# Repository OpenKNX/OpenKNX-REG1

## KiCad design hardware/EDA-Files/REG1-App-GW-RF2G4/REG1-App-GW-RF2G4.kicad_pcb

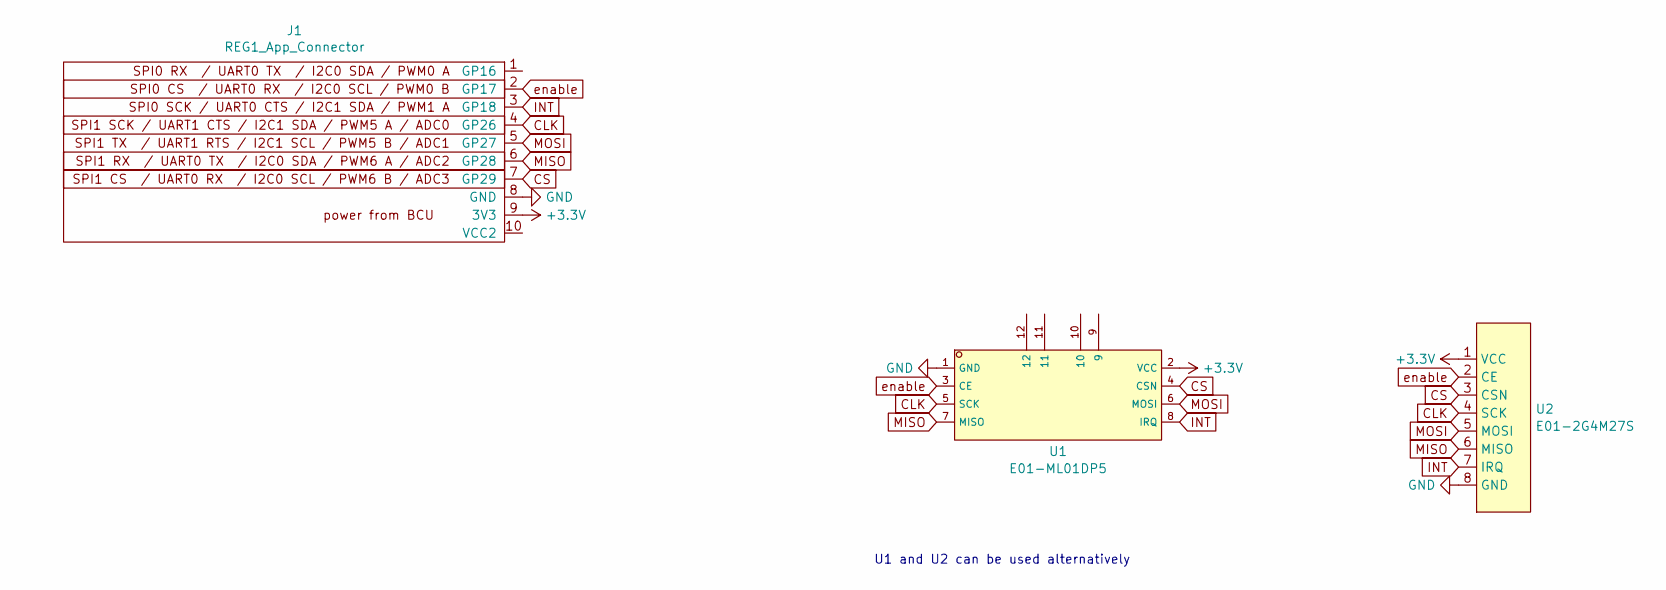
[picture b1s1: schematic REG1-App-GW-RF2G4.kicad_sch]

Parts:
J1: REG1_App_Connector; PinHeader_1x10_P2.54mm_Horizontal
U1: E01-ML01DP5; WIRELM-TH_E01-ML01DP5; LCSC C97339
U2: E01-2G4M27S; C2971732_WIRELM-SMD_10P-L23.0-W14.0-P1.27_E01-2G4M27S_Hands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; LCSC Part C2971732

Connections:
+3.3V: J1.9 (3V3), U1.2 (VCC), U2.1 (VCC)
CLK: J1.4 (GP26), U1.5 (SCK), U2.4 (SCK)
CS: J1.7 (GP29), U1.4 (CSN), U2.3 (CSN)
GND: J1.8 (GND), U1.1 (GND), U2.8 (GND), U2.9 (GND), U2.10 (GND)
INT: J1.3 (GP18), U1.8 (IRQ), U2.7 (IRQ)
MISO: J1.6 (GP28), U1.7 (MISO), U2.6 (MISO)
MOSI: J1.5 (GP27), U1.6 (MOSI), U2.5 (MOSI)
enable: J1.2 (GP17), U1.3 (CE), U2.2 (CE)

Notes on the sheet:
U1 and U2 can be used alternatively

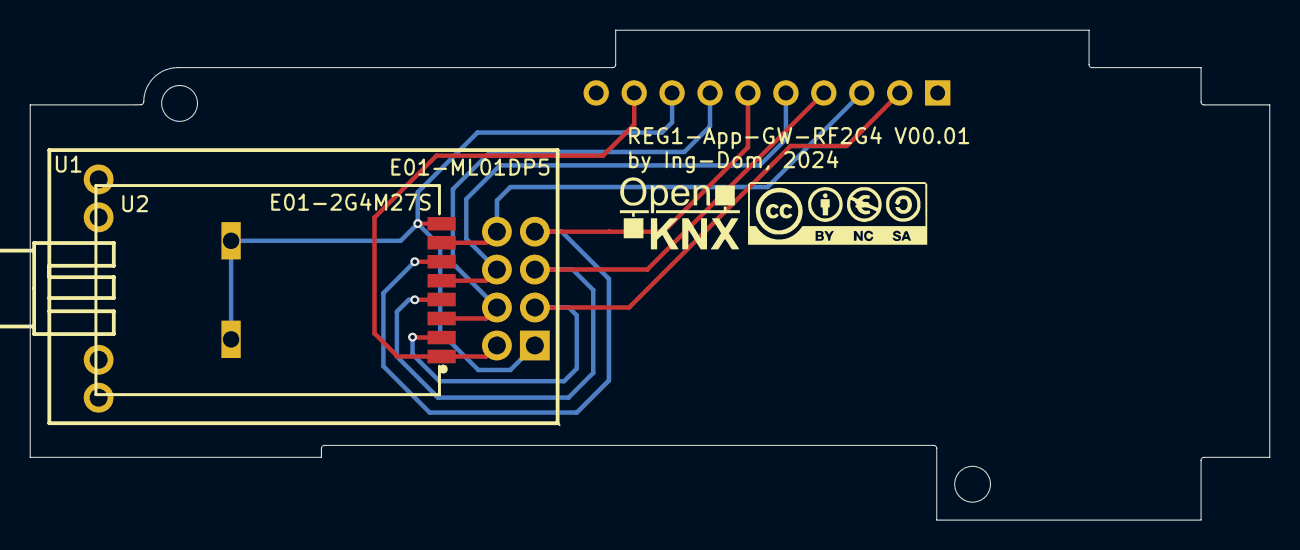
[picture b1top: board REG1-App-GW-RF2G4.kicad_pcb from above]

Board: 2 copper layers, 83.0 x 32.8 mm, 4 parts (1 on the bottom side), 8 nets.

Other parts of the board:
G1: LOGO; CC-BY-NY-SA_12x4

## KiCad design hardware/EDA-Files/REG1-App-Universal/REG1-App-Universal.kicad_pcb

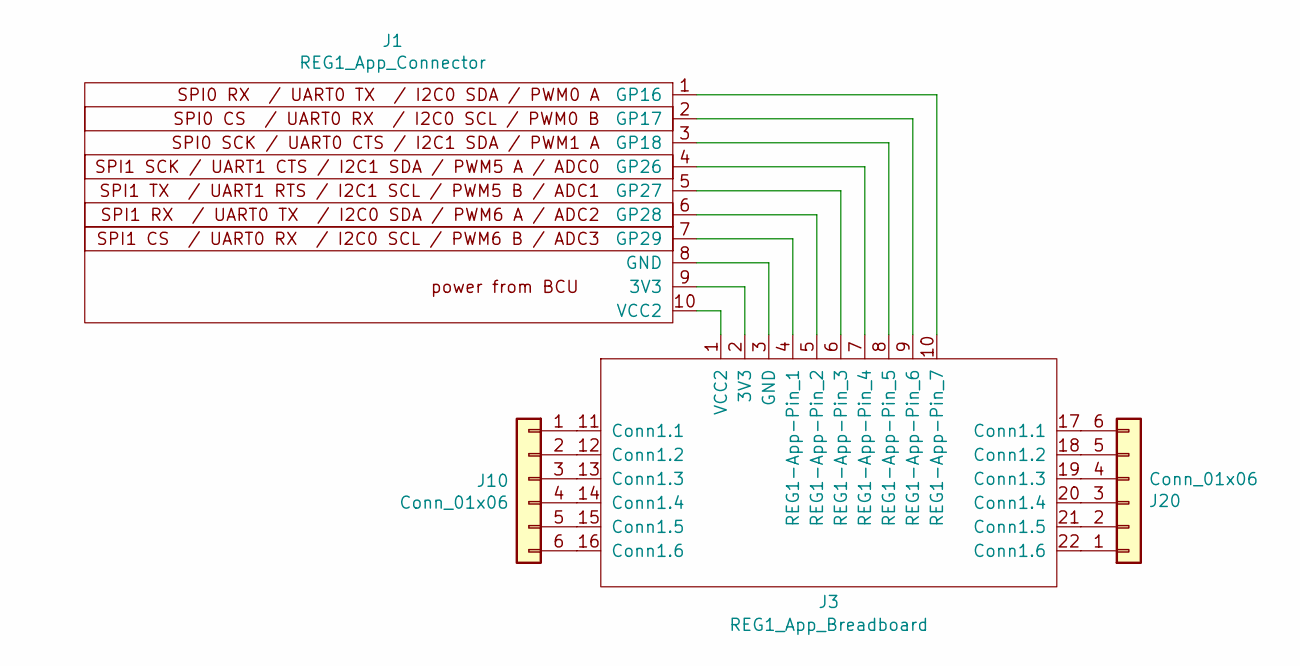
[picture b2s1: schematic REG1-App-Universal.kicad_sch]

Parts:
J1: REG1_App_Connector; PinHeader_1x10_P2.54mm_Horizontal; LCSC C706873
J3: REG1_App_Breadboard
J10, J20: Conn_01x06; PhoenixContact_MC_1,5_6-G-3.5_1x06_P3.50mm_Horizontal; LCSC C441175

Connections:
unnamed: J1.9 (3V3), J3.2 (3V3)
unnamed: J1.8 (GND), J3.3 (GND)
unnamed: J1.1 (GP16), J3.10 (REG1-App-Pin_7)
unnamed: J1.2 (GP17), J3.9 (REG1-App-Pin_6)
unnamed: J1.3 (GP18), J3.8 (REG1-App-Pin_5)
unnamed: J1.4 (GP26), J3.7 (REG1-App-Pin_4)
unnamed: J1.5 (GP27), J3.6 (REG1-App-Pin_3)
unnamed: J1.6 (GP28), J3.5 (REG1-App-Pin_2)
unnamed: J1.7 (GP29), J3.4 (REG1-App-Pin_1)
unnamed: J1.10 (VCC2), J3.1 (VCC2)
unnamed: J3.11 (Conn1.1), J10.1
unnamed: J3.12 (Conn1.2), J10.2
unnamed: J3.13 (Conn1.3), J10.3
unnamed: J3.14 (Conn1.4), J10.4
unnamed: J3.15 (Conn1.5), J10.5
unnamed: J3.16 (Conn1.6), J10.6
unnamed: J3.22 (Conn1.6), J20.1
unnamed: J3.21 (Conn1.5), J20.2
unnamed: J3.20 (Conn1.4), J20.3
unnamed: J3.19 (Conn1.3), J20.4
unnamed: J3.18 (Conn1.2), J20.5
unnamed: J3.17 (Conn1.1), J20.6

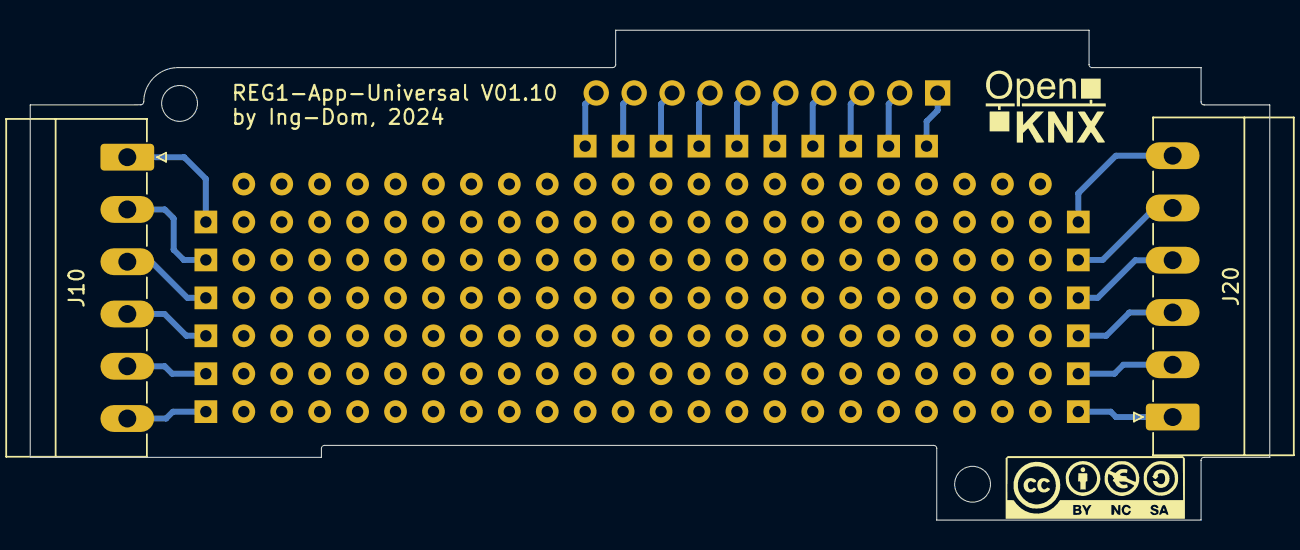
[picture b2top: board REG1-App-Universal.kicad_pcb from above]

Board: 2 copper layers, 83.0 x 32.8 mm, 6 parts (1 on the bottom side), 22 nets.

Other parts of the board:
G*: LOGO; CC-BY-NY-SA_12x4
G*#2: LOGO; OpenKNX_Logo_10x10

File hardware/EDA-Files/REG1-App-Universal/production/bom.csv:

Designator,Footprint,Quantity,Value,LCSC Part #
J1,PinHeader_1x10_P2.54mm_Horizontal,1,REG1_App_Connector,C706873
"J10, J20","PhoenixContact_MC_1,5_6-G-3.5_1x06_P3.50mm_Horizontal",2,Conn_01x06,C441175
J3,REG1_App_Breadboard,1,REG1_App_Breadboard,

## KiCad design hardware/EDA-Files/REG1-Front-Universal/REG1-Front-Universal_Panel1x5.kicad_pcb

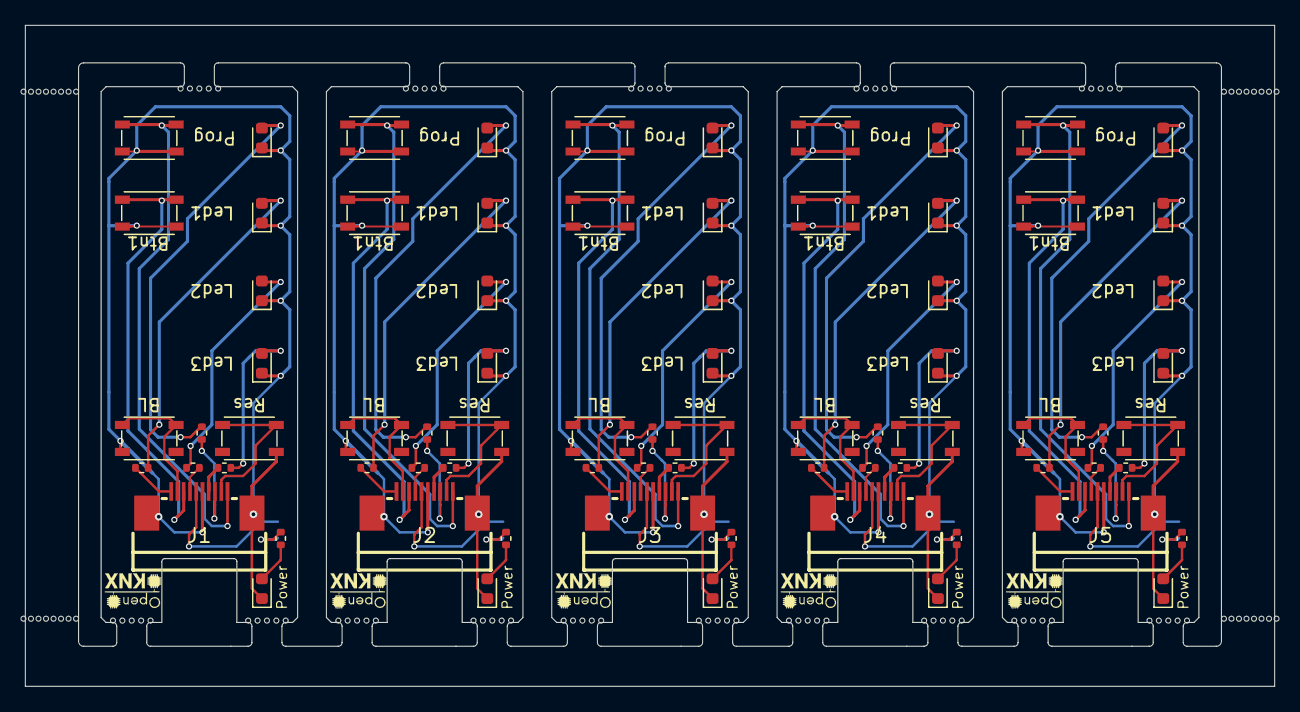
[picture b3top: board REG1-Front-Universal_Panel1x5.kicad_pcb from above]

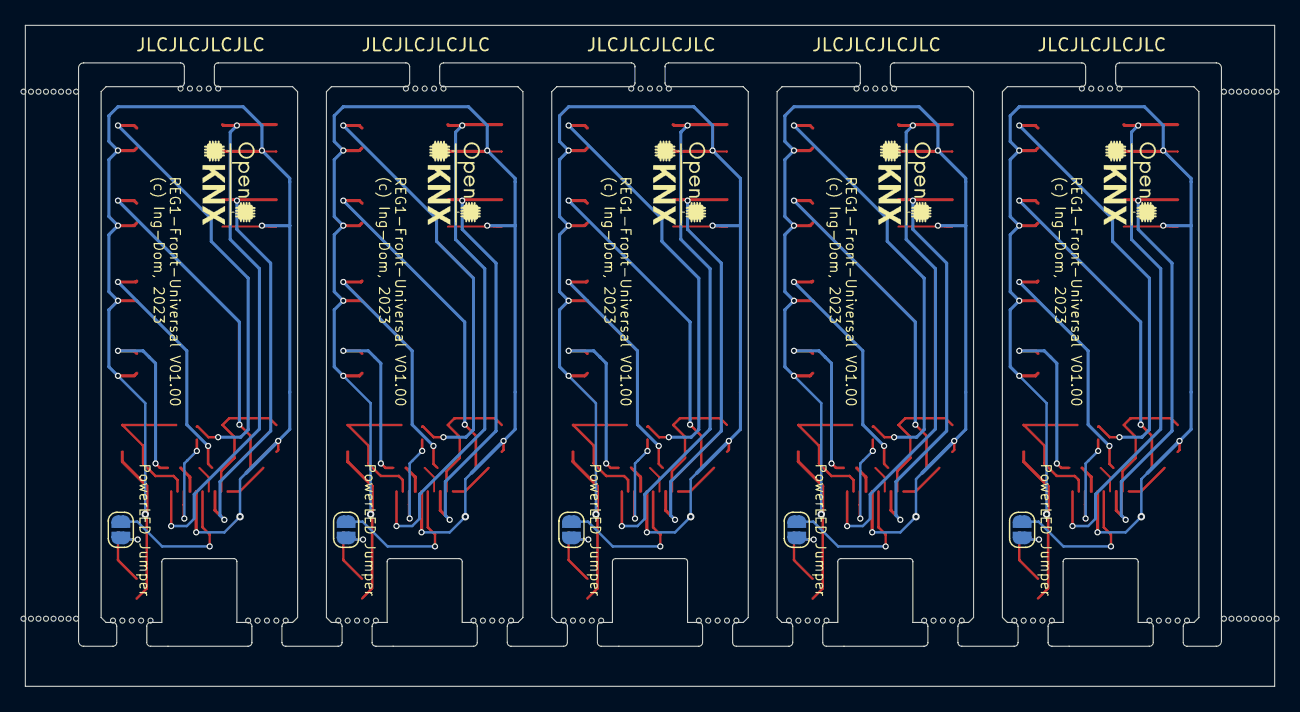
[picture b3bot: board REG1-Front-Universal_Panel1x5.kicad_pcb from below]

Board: 2 copper layers, 99.8 x 52.8 mm, 99 parts (5 on the bottom side), 16 nets.

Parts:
D1, D6, D11, D16, D21: Prog; LED_0603_1608Metric
D2, D7, D12, D17, D22: Led1; LED_0603_1608Metric
D3, D8, D13, D18, D23: Led2; LED_0603_1608Metric
D4, D9, D14, D19, D24: Led3; LED_0603_1608Metric
D5, D10, D15, D20, D25: Power; LED_0603_1608Metric
J1, J2, J3, J4, J5: Frontpanel; C11050_FPC-SMD_P0.5-10P_LSXJ-H2.0-10P
JP1, JP2, JP3, JP4, JP5: PowerLED Jumper; SolderJumper-2_P1.3mm_Open_RoundedPad1.0x1.5mm
R1, R2, R3, R4, R5, R6, R7, R8, R9, R10, R11, R12, R13, R14, R15, R16, R17, R18, R19, R20, R21, R22, R23, R24, R25: 2k2; R_0402_1005Metric
SW1, SW5, SW9, SW13, SW17: Prog; C455282_SW-SMD_4P-L4.2-W3.3-P2.15-LS5.1
SW2, SW6, SW10, SW14, SW18: Btn1; C455282_SW-SMD_4P-L4.2-W3.3-P2.15-LS5.1
SW3, SW7, SW11, SW15, SW19: Res; C455282_SW-SMD_4P-L4.2-W3.3-P2.15-LS5.1
SW4, SW8, SW12, SW16, SW20: BL; C455282_SW-SMD_4P-L4.2-W3.3-P2.15-LS5.1
e: VAL**; mouse-bite-5.00mm-frame
e#2: VAL**; mouse-bite-5.00mm-frame
mouse-bite, mouse-bite1, mouse-bite2, mouse-bite3, mouse-bite4, mouse-bite5, mouse-bite6, mouse-bite7, mouse-bite8, mouse-bite9, mouse-bite10, mouse-bite11, mouse-bite12: mouse-bite-2.00mm-slot_1side
mouse-bite#2, mouse-bite#4: VAL**; mouse-bite-5.00mm-frame
mouse-bite#3, mouse-bite#5: mouse-bite-2.00mm-slot_1side

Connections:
+3.3V: J1.6, J2.6, J3.6, J4.6, J5.6, JP1.2 (B), JP2.2 (B), JP3.2 (B), JP4.2 (B), JP5.2 (B)
BOOTSEL: J1.9, J2.9, J3.9, J4.9, J5.9, SW4.1, SW8.1, SW12.1, SW16.1, SW20.1
GND: D1.1 (K), D2.1 (K), D3.1 (K), D4.1 (K), D5.1 (K), D6.1 (K), D7.1 (K), D8.1 (K), D9.1 (K), D10.1 (K), D11.1 (K), D12.1 (K), D13.1 (K), D14.1 (K), D15.1 (K), D16.1 (K), D17.1 (K), D18.1 (K), D19.1 (K), D20.1 (K), D21.1 (K), D22.1 (K), D23.1 (K), D24.1 (K), D25.1 (K), J1.5, J1.11, J1.12, J2.5, J2.11, J2.12, J3.5, J3.11, J3.12, J4.5, J4.11, J4.12, J5.5, J5.11, J5.12, SW1.2, SW2.2, SW3.2, SW4.2, SW5.2, SW6.2, SW7.2, SW8.2, SW9.2, SW10.2, SW11.2, SW12.2, SW13.2, SW14.2, SW15.2, SW16.2, SW17.2, SW18.2, SW19.2, SW20.2
GPIO6: J1.10, J2.10, J3.10, J4.10, J5.10, R2.2, R7.2, R12.2, R17.2, R22.2
GPIO7: J1.8, J2.8, J3.8, J4.8, J5.8, SW2.1, SW6.1, SW10.1, SW14.1, SW18.1
GPIO22: J1.4, J2.4, J3.4, J4.4, J5.4, R4.2, R9.2, R14.2, R19.2, R24.2
GPIO23: J1.1, J2.1, J3.1, J4.1, J5.1, SW1.1, SW5.1, SW9.1, SW13.1, SW17.1
GPIO24: J1.7, J2.7, J3.7, J4.7, J5.7, R3.2, R8.2, R13.2, R18.2, R23.2
GPIO25: J1.3, J2.3, J3.3, J4.3, J5.3, R1.2, R6.2, R11.2, R16.2, R21.2
unnamed: D1.2 (A), D6.2 (A), D11.2 (A), D16.2 (A), D21.2 (A), R1.1, R6.1, R11.1, R16.1, R21.1
unnamed: D2.2 (A), D7.2 (A), D12.2 (A), D17.2 (A), D22.2 (A), R2.1, R7.1, R12.1, R17.1, R22.1
unnamed: D3.2 (A), D8.2 (A), D13.2 (A), D18.2 (A), D23.2 (A), R3.1, R8.1, R13.1, R18.1, R23.1
unnamed: D4.2 (A), D9.2 (A), D14.2 (A), D19.2 (A), D24.2 (A), R4.1, R9.1, R14.1, R19.1, R24.1
unnamed: D5.2 (A), D10.2 (A), D15.2 (A), D20.2 (A), D25.2 (A), R5.1, R10.1, R15.1, R20.1, R25.1
unnamed: JP1.1 (A), JP2.1 (A), JP3.1 (A), JP4.1 (A), JP5.1 (A), R5.2, R10.2, R15.2, R20.2, R25.2
RUN: J1.2, J2.2, J3.2, J4.2, J5.2, SW3.1, SW7.1, SW11.1, SW15.1, SW19.1

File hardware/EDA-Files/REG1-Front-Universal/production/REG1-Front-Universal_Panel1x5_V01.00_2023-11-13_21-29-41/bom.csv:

Designator,Footprint,Quantity,Value,LCSC Part #
"D1, D11, D16, D21, D6",0603,5,Prog,C2286
"D10, D15, D20, D25, D5",0603,5,Power,C72043
"D12, D17, D2, D22, D7",0603,5,Led1,C72043
"D13, D18, D23, D3, D8",0603,5,Led2,C72043
"D14, D19, D24, D4, D9",0603,5,Led3,C72043
"J1, J2, J3, J4, J5",C11050_FPC-SMD_P0.5-10P_LSXJ-H2.0-10P,5,Frontpanel,C11050
"R1, R10, R11, R12, R13, R14, R15, R16, R17, R18, R19, R2, R20, R21, R22, R23, R24, R25, R3, R4, R5, R6, R7, R8, R9",0402,25,2k2,C25879
"SW1, SW13, SW17, SW5, SW9",C455282_SW-SMD_4P-L4.2-W3.3-P2.15-LS5.1,5,Prog,C455282
"SW10, SW14, SW18, SW2, SW6",C455282_SW-SMD_4P-L4.2-W3.3-P2.15-LS5.1,5,Btn1,C455282
"SW11, SW15, SW19, SW3, SW7",C455282_SW-SMD_4P-L4.2-W3.3-P2.15-LS5.1,5,Res,C455282
"SW12, SW16, SW20, SW4, SW8",C455282_SW-SMD_4P-L4.2-W3.3-P2.15-LS5.1,5,BL,C455282

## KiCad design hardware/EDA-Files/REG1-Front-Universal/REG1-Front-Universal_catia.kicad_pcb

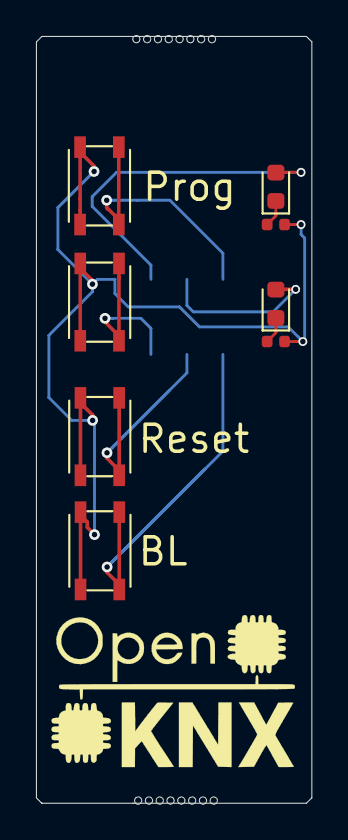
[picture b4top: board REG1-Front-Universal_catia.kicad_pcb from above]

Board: 2 copper layers, 15.3 x 42.6 mm, 11 parts (1 on the bottom side), 9 nets.

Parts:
D1: Prog; LED_0603_1608Metric
D2: Func; LED_0603_1608Metric
J1: Conn_02x04_Odd_Even; PinHeader_2x04_P2.00mm_Vertical_SMD
R1, R2: R; R_0402_1005Metric
SW1: Prog; SW_Push_Xunpu_TS-1089S
SW2: Func; SW_Push_Xunpu_TS-1089S
SW3: Res; SW_Push_Xunpu_TS-1089S
SW4: BL; SW_Push_Xunpu_TS-1089S
mouse-bite: VAL**; mouse-bite-5.00mm-frame
mouse-bite#2: VAL**; mouse-bite-5.00mm-frame

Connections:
BOOTSEL_F: J1.8, SW4.1
GND: J1.1, R1.1, R2.1, SW1.2, SW2.2, SW3.2, SW4.2
GPIO03: D2.2, J1.5
GPIO24: J1.4, SW2.1
unnamed: D1.1, R1.2
unnamed: D2.1, R2.2
PROGBTN: J1.7, SW1.1
PROGLED: D1.2, J1.3
RUN: J1.6, SW3.1

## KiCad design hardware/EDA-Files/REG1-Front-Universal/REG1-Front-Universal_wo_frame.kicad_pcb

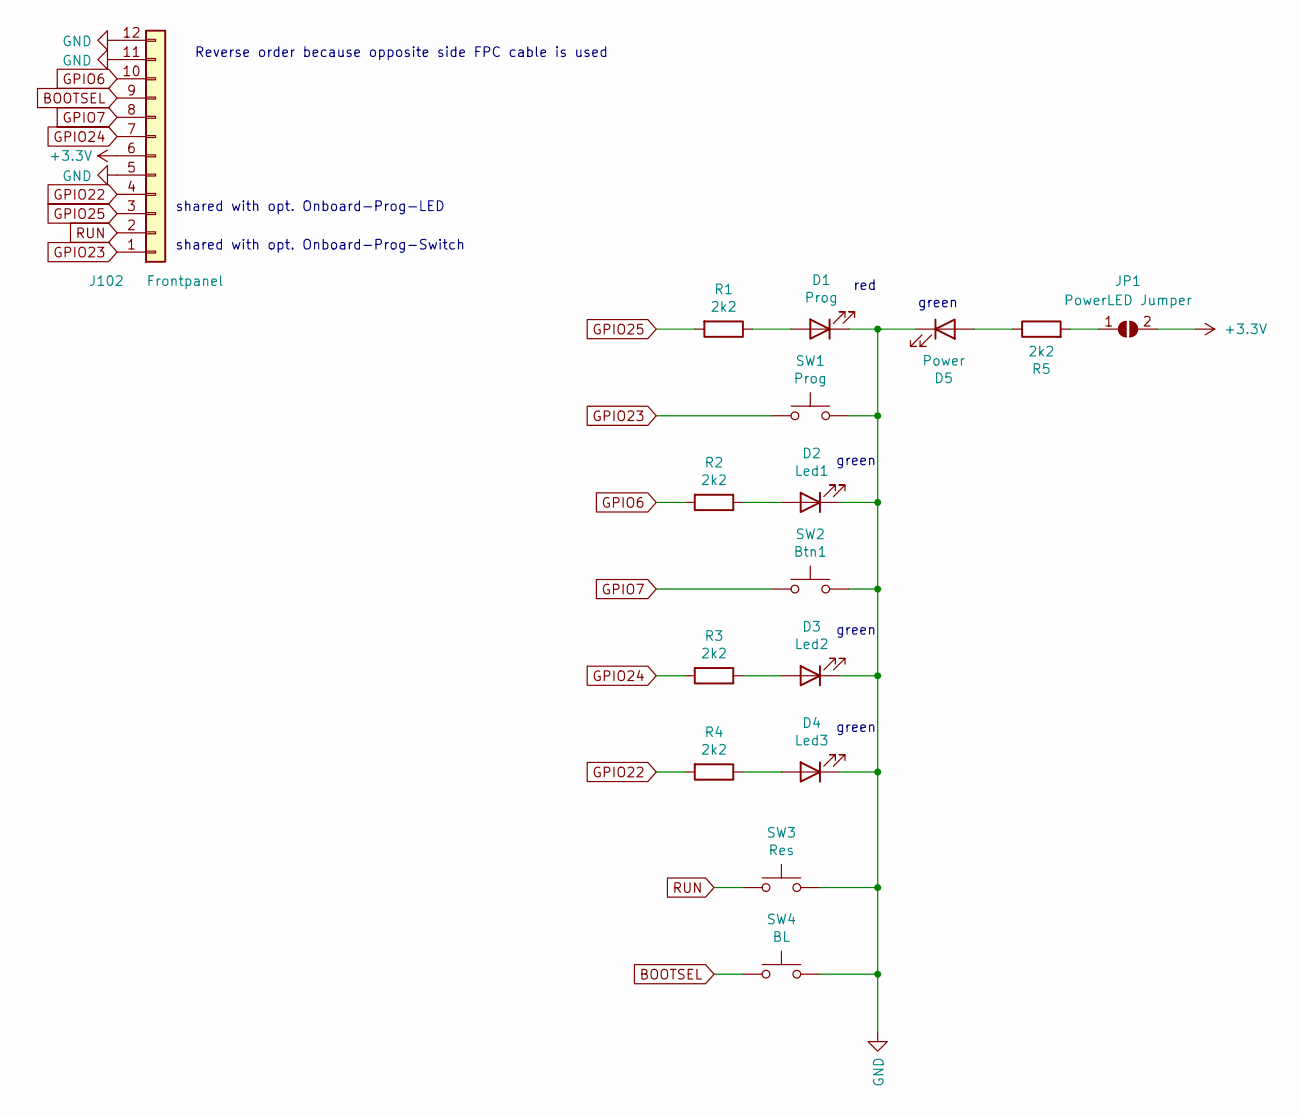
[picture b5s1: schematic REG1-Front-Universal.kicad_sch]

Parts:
D1: Prog; LED_0603_1608Metric; LCSC C2286
D2: Led1; LED_0603_1608Metric; LCSC C72043
D3: Led2; LED_0603_1608Metric; LCSC C72043
D4: Led3; LED_0603_1608Metric; LCSC C72043
D5: Power; LED_0603_1608Metric; LCSC C72043
J102: Frontpanel; C11050_FPC-SMD_P0.5-10P_LSXJ-H2.0-10P; LCSC C11050
JP1: PowerLED Jumper; SolderJumper-2_P1.3mm_Open_RoundedPad1.0x1.5mm
R1, R2, R3, R4, R5: 2k2; R_0402_1005Metric; LCSC C25879
SW1: Prog; C455282_SW-SMD_4P-L4.2-W3.3-P2.15-LS5.1; LCSC C455282
SW2: Btn1; C455282_SW-SMD_4P-L4.2-W3.3-P2.15-LS5.1; LCSC C455282
SW3: Res; C455282_SW-SMD_4P-L4.2-W3.3-P2.15-LS5.1; LCSC C455282
SW4: BL; C455282_SW-SMD_4P-L4.2-W3.3-P2.15-LS5.1; LCSC C455282

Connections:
+3.3V: JP1.2 (B); also elsewhere on the board
BOOTSEL: SW4.1; also elsewhere on the board
GND: D1.1 (K), D2.1 (K), D3.1 (K), D4.1 (K), D5.1 (K), SW1.2, SW2.2, SW3.2, SW4.2; also elsewhere on the board
GPIO6: R2.2; also elsewhere on the board
GPIO7: SW2.1; also elsewhere on the board
GPIO22: R4.2; also elsewhere on the board
GPIO23: SW1.1; also elsewhere on the board
GPIO24: R3.2; also elsewhere on the board
GPIO25: R1.2; also elsewhere on the board
unnamed: D1.2 (A), R1.1
unnamed: D2.2 (A), R2.1
unnamed: D3.2 (A), R3.1
unnamed: D4.2 (A), R4.1
unnamed: D5.2 (A), R5.1
unnamed: JP1.1 (A), R5.2
RUN: SW3.1; also elsewhere on the board

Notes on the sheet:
green
red
Reverse order because opposite side FPC cable is used
shared with opt. Onboard-Prog-Switch
shared with opt. Onboard-Prog-LED

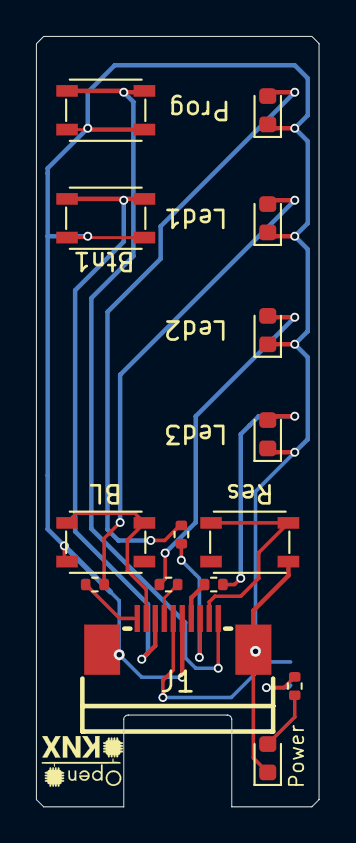
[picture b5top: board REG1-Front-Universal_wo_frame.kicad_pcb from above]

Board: 2 copper layers, 15.7 x 42.8 mm, 16 parts (1 on the bottom side), 16 nets.

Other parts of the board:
J1: Frontpanel; C11050_FPC-SMD_P0.5-10P_LSXJ-H2.0-10P

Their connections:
+3.3V: J1.6; also elsewhere on the board
BOOTSEL: J1.9; also elsewhere on the board
GND: J1.5, J1.11, J1.12; also elsewhere on the board
GPIO6: J1.10; also elsewhere on the board
GPIO7: J1.8; also elsewhere on the board
GPIO22: J1.4; also elsewhere on the board
GPIO23: J1.1; also elsewhere on the board
GPIO24: J1.7; also elsewhere on the board
GPIO25: J1.3; also elsewhere on the board
RUN: J1.2; also elsewhere on the board

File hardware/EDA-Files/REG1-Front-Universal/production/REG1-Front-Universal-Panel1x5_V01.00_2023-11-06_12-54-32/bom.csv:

Designator,Footprint,Quantity,Value,LCSC Part #
"D1_5, D1_4, D1_3, D1_2, D1",0603,5,Prog,C2286
"D2_5, D2_4, D2_3, D2_2, D2",0603,5,Led1,C72043
"D3_5, D3_4, D3_3, D3_2, D3",0603,5,Led2,C72043
"D4_5, D4_4, D4_3, D4_2, D4",0603,5,Led3,C72043
"D5_5, D5_4, D5_3, D5_2, D5",0603,5,Power,C72043
"J1_5, J1_4, J1_3, J1_2, J1",C11050_FPC-SMD_P0.5-10P_LSXJ-H2.0-10P,5,Frontpanel,C11050
"R1_5, R1_4, R1_3, R1_2, R1, R2_5, R2_4, R2_3, R2_2, R2, R3_5, R3_4, R3_3, R3_2, R3, R4_5, R4_4, R4_3, R4_2, R4, R5_5, R5_4, R5_3, R5_2, R5",0402,25,2k2,C25879
"SW1_5, SW1_4, SW1_3, SW1_2, SW1",C455282_SW-SMD_4P-L4.2-W3.3-P2.15-LS5.1,5,Prog,C455282
"SW2_5, SW2_4, SW2_3, SW2_2, SW2",C455282_SW-SMD_4P-L4.2-W3.3-P2.15-LS5.1,5,Btn1,C455282
"SW3_5, SW3_4, SW3_3, SW3_2, SW3",C455282_SW-SMD_4P-L4.2-W3.3-P2.15-LS5.1,5,Res,C455282
"SW4_5, SW4_4, SW4_3, SW4_2, SW4",C455282_SW-SMD_4P-L4.2-W3.3-P2.15-LS5.1,5,BL,C455282

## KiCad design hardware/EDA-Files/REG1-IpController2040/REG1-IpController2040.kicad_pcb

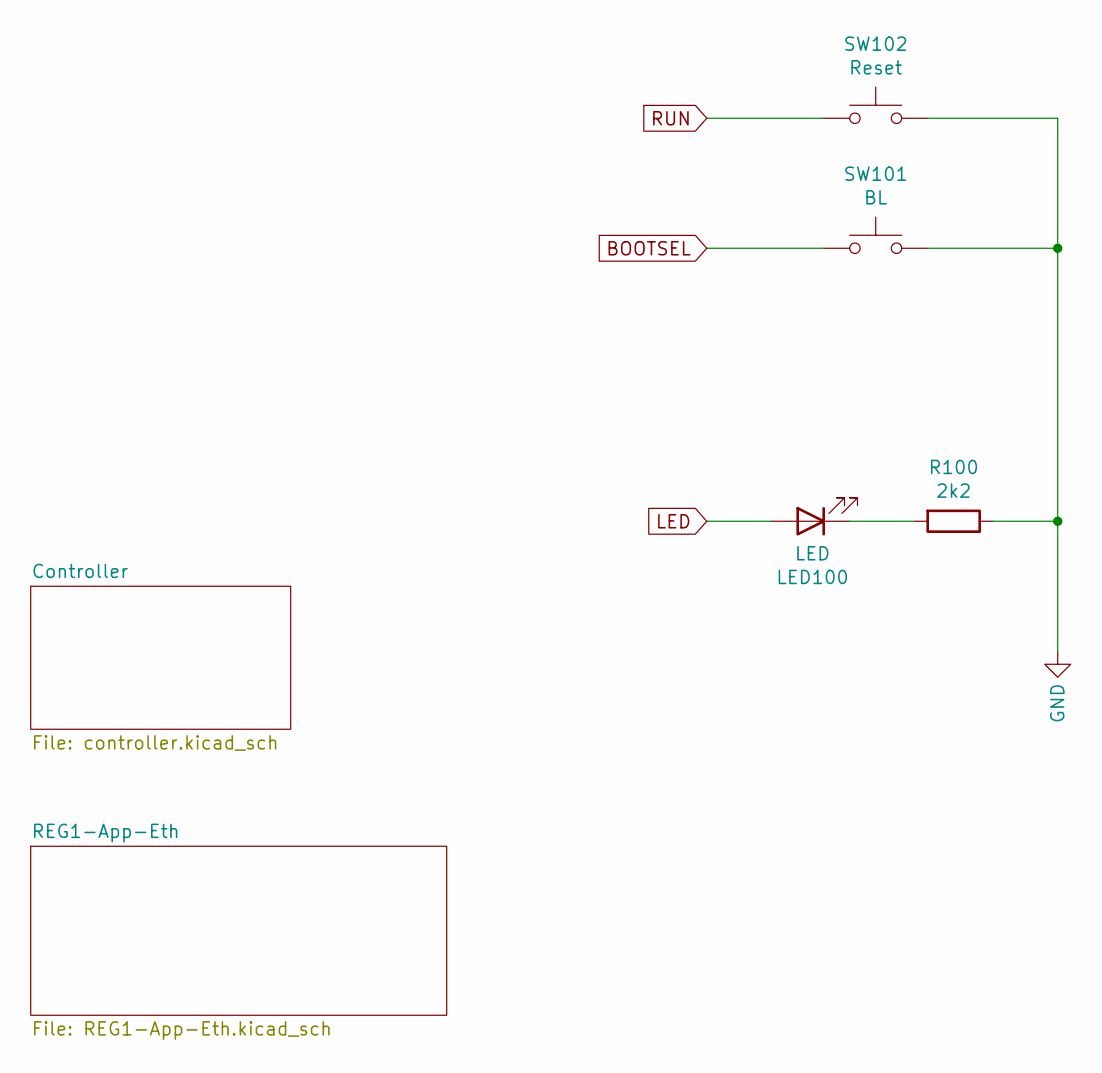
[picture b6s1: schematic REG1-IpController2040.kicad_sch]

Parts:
LED100: LED; D_0603_1608Metric
R100: 2k2; R_0402_1005Metric
SW101: BL; C455282_SW-SMD_4P-L4.2-W3.3-P2.15-LS5.1_Handsolder
SW102: Reset; C455282_SW-SMD_4P-L4.2-W3.3-P2.15-LS5.1_Handsolder

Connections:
BOOTSEL: SW101.1; also elsewhere on the board
GND: R100.1, SW101.2, SW102.2; also elsewhere on the board
LED: LED100.2 (A); also elsewhere on the board
unnamed: LED100.1 (K), R100.2
RUN: SW102.1; also elsewhere on the board

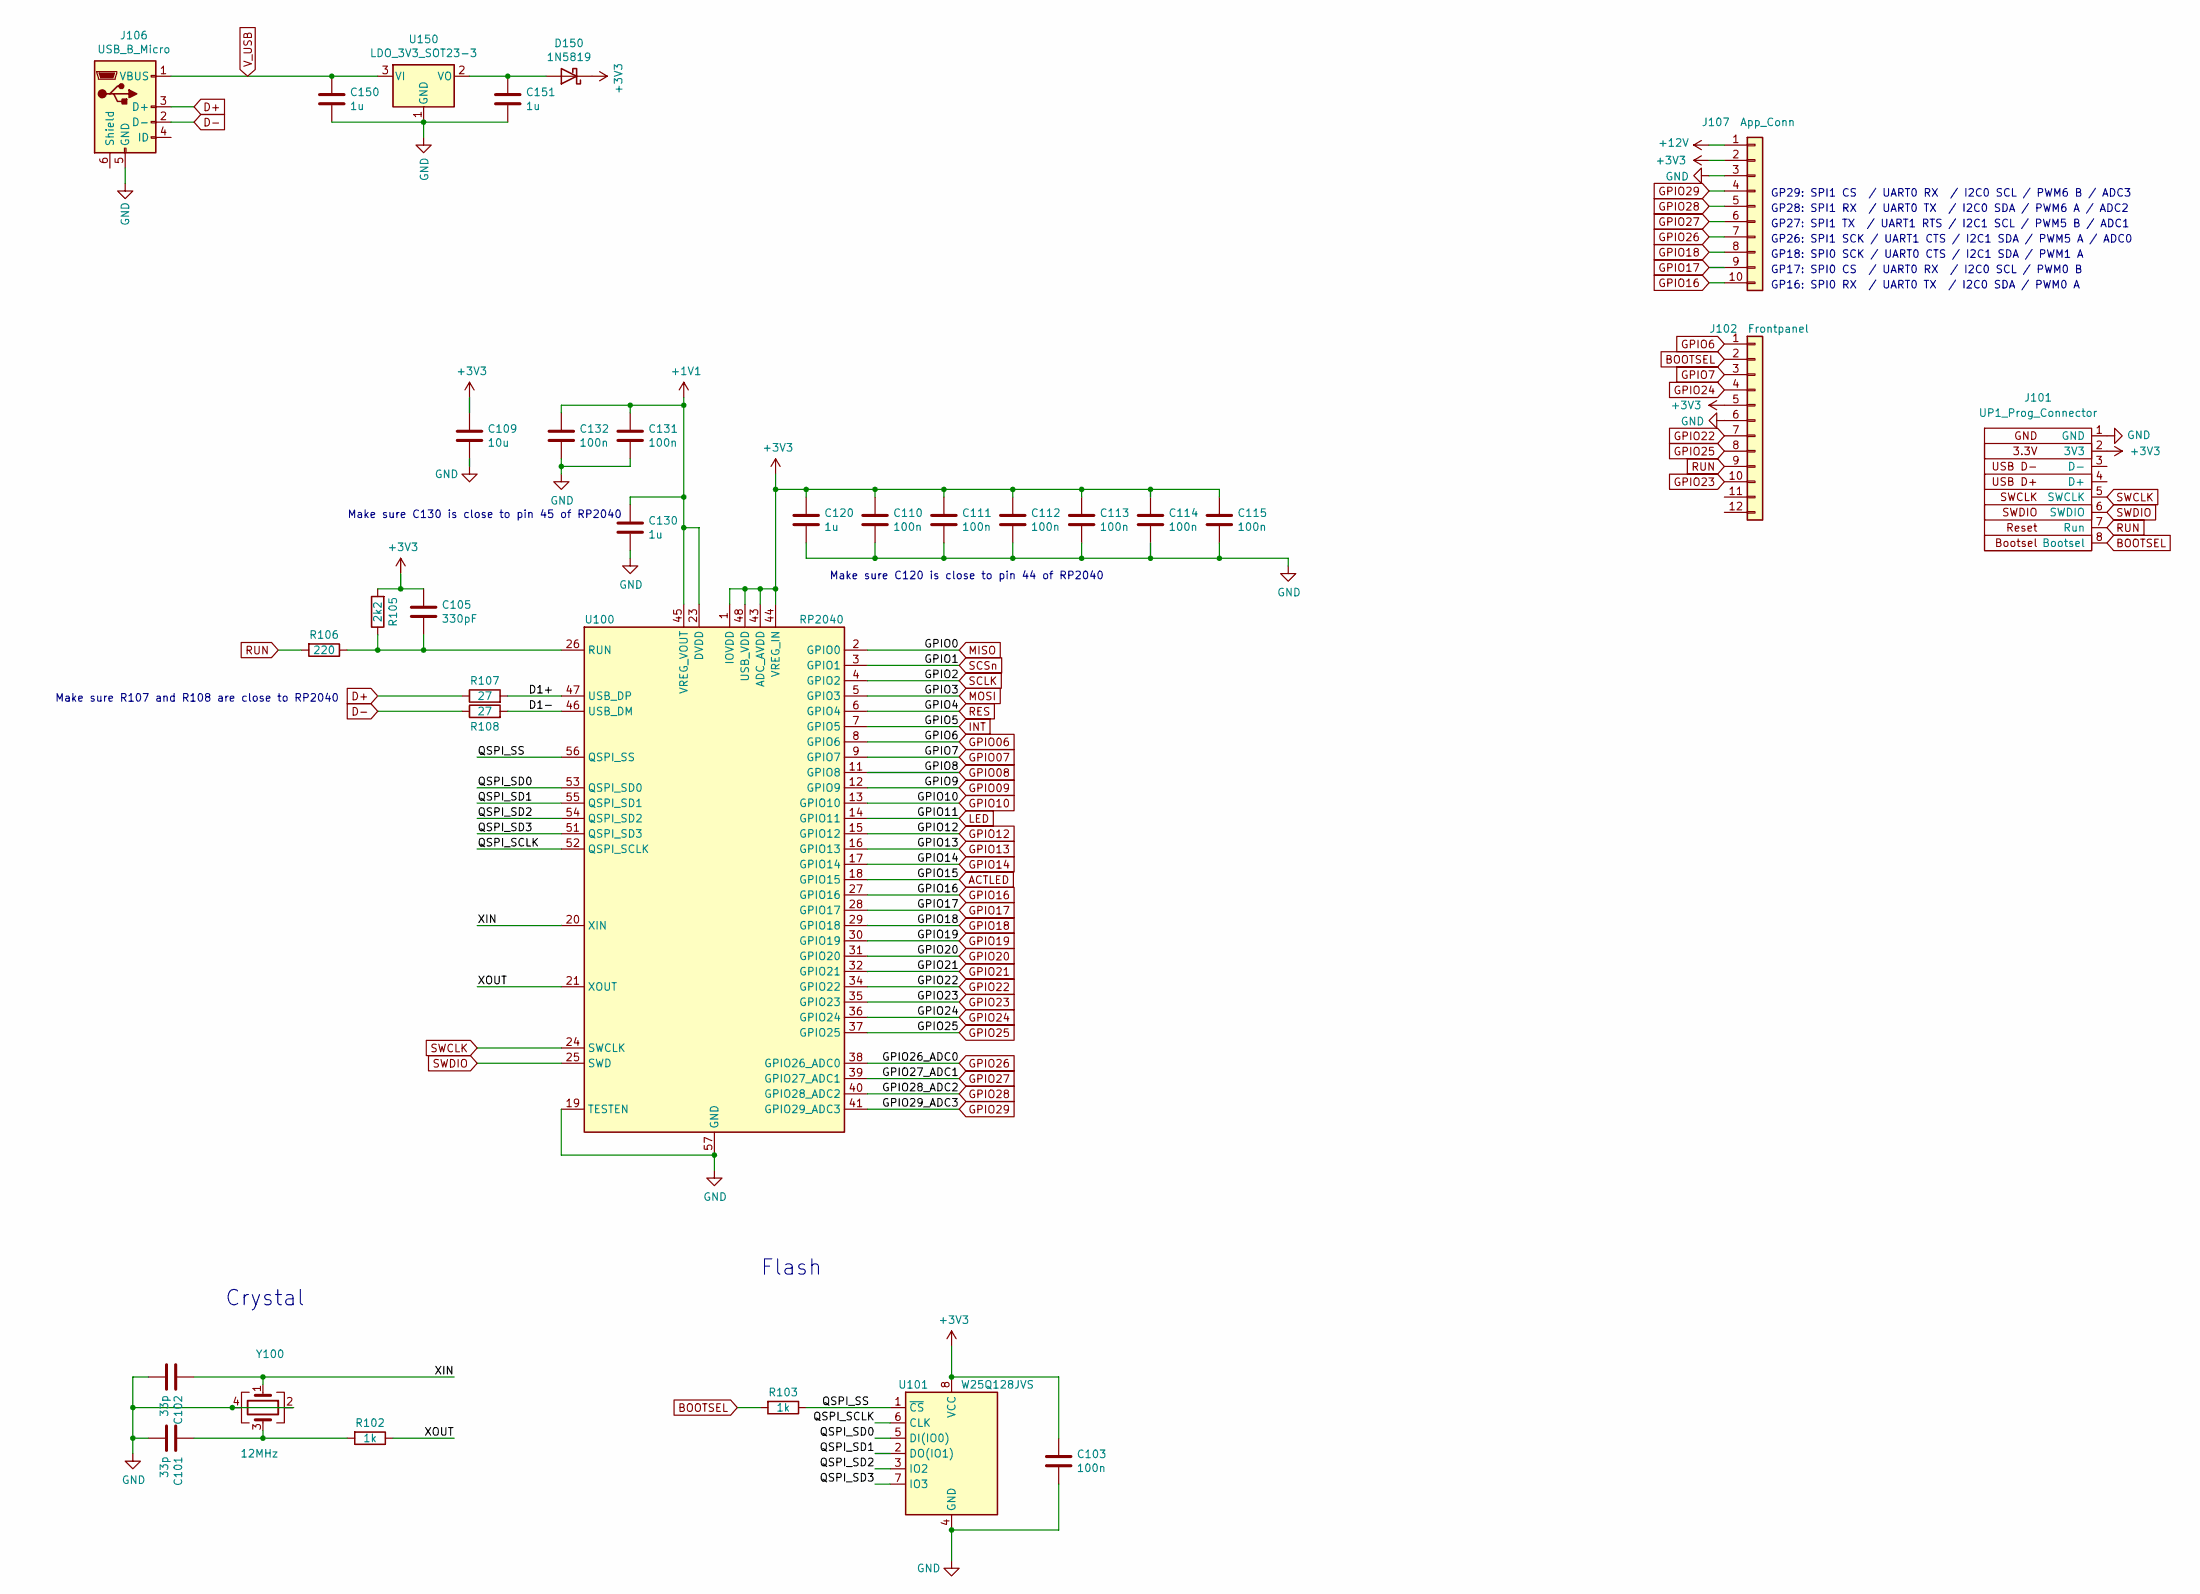
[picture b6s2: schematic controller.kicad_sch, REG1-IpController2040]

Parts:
C101, C102: 33p; C_0402_1005Metric
C103, C110, C111, C112, C113, C114, C115, C131, C132: 100n; C_0402_1005Metric
C105: 330pF; C_0402_1005Metric
C109: 10u; C_0805_2012Metric
C120, C130, C150, C151: 1u; C_0402_1005Metric
D150: 1N5819; D_SOD-323
J101: UP1_Prog_Connector; CONN-SMD_8P-P1.25-L4.4-W14.8_reversed
J102: Frontpanel; CONN-TH-10P_AFC11-S10ICC-00
J106: USB_B_Micro; USB_Micro-B_JING_C10418
J107: App_Conn; PinHeader_1x10_P2.54mm_Vertical
R102, R103: 1k; R_0402_1005Metric
R105: 2k2; R_0402_1005Metric
R106: 220; R_0402_1005Metric
R107, R108: 27; C_0402_1005Metric
U100: RP2040; RP2040-QFN-56_modified
U101: W25Q128JVS; WSON-8-1EP_6x5mm_P1.27mm
U150: LDO_3V3_SOT23-3; SOT-23
Y100: 12MHz; Crystal_SMD_3225-4Pin_3.2x2.5mm

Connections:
+1V1: C130.1, C131.1, C132.1, U100.23 (DVDD), U100.45 (VREG_VOUT), U100.50 (DVDD)
+3V3: C103.1, C105.1, C109.1, C110.1, C111.1, C112.1, C113.1, C114.1, C115.1, C120.1, D150.1 (K), J101.2 (3V3), J102.5, J107.2, R105.2, U100.1 (IOVDD), U100.10 (IOVDD), U100.22 (IOVDD), U100.33 (IOVDD), U100.42 (IOVDD), U100.43 (ADC_AVDD), U100.44 (VREG_IN), U100.48 (USB_VDD), U100.49 (IOVDD), U101.8 (VCC); also elsewhere on the board
+12V: J107.1; also elsewhere on the board
/Controller/D1+: R107.2, U100.47 (USB_DP)
/Controller/D1-: R108.2, U100.46 (USB_DM)
/Controller/QSPI_SCLK: U100.52 (QSPI_SCLK), U101.6 (CLK)
/Controller/QSPI_SD0: U100.53 (QSPI_SD0), U101.5 (DI(IO0))
/Controller/QSPI_SD1: U100.55 (QSPI_SD1), U101.2 (DO(IO1))
/Controller/QSPI_SD2: U100.54 (QSPI_SD2), U101.3 (IO2)
/Controller/QSPI_SD3: U100.51 (QSPI_SD3), U101.7 (IO3)
/Controller/QSPI_SS: R103.1, U100.56 (QSPI_SS), U101.1 (~CS)
/Controller/XIN: C102.1, U100.20 (XIN), Y100.1
/Controller/XOUT: R102.1, U100.21 (XOUT)
ACTLED: U100.18 (GPIO15); also elsewhere on the board
BOOTSEL: J101.8 (Bootsel), J102.2, R103.2; also elsewhere on the board
D+: J106.3 (D+), R107.1
D-: J106.2 (D-), R108.1
GND: C101.2, C102.2, C103.2, C109.2, C110.2, C111.2, C112.2, C113.2, C114.2, C115.2, C120.2, C130.2, C131.2, C132.2, C150.2, C151.2, J101.1 (GND), J102.6, J106.5 (GND), J107.3, U100.19 (TESTEN), U100.57 (GND), U101.4 (GND), U150.1 (GND), Y100.2, Y100.4; also elsewhere on the board
GPIO06: J102.1, U100.8 (GPIO6)
GPIO07: J102.3, U100.9 (GPIO7)
GPIO08: U100.11 (GPIO8)
GPIO09: U100.12 (GPIO9)
GPIO10: U100.13 (GPIO10)
GPIO12: U100.15 (GPIO12)
GPIO13: U100.16 (GPIO13)
GPIO14: U100.17 (GPIO14)
GPIO16: J107.10, U100.27 (GPIO16)
GPIO17: J107.9, U100.28 (GPIO17)
GPIO18: J107.8, U100.29 (GPIO18)
GPIO19: U100.30 (GPIO19)
GPIO20: U100.31 (GPIO20)
GPIO21: U100.32 (GPIO21)
GPIO22: J102.7, U100.34 (GPIO22)
GPIO23: J102.10, U100.35 (GPIO23)
GPIO24: J102.4, U100.36 (GPIO24)
GPIO25: J102.8, U100.37 (GPIO25)
GPIO26: J107.7, U100.38 (GPIO26_ADC0)
GPIO27: J107.6, U100.39 (GPIO27_ADC1)
GPIO28: J107.5, U100.40 (GPIO28_ADC2)
GPIO29: J107.4, U100.41 (GPIO29_ADC3)
INT: U100.7 (GPIO5); also elsewhere on the board
LED: U100.14 (GPIO11); also elsewhere on the board
MISO: U100.2 (GPIO0); also elsewhere on the board
MOSI: U100.5 (GPIO3); also elsewhere on the board
unnamed: C101.1, R102.2, Y100.3
unnamed: C151.1, D150.2 (A), U150.2 (VO)
unnamed: C105.2, R105.1, R106.1, U100.26 (RUN)
RES: U100.6 (GPIO4); also elsewhere on the board
RUN: J101.7 (Run), J102.9, R106.2; also elsewhere on the board
SCLK: U100.4 (GPIO2); also elsewhere on the board
SCSn: U100.3 (GPIO1); also elsewhere on the board
SWCLK: J101.5 (SWCLK), U100.24 (SWCLK)
SWDIO: J101.6 (SWDIO), U100.25 (SWD)
V_USB: C150.1, J106.1 (VBUS), U150.3 (VI)

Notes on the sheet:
GP28: SPI1 RX / UART0 TX / I2C0 SDA / PWM6 A / ADC2
Make sure R107 and R108 are close to RP2040
Crystal
GP16: SPI0 RX / UART0 TX / I2C0 SDA / PWM0 A
GP29: SPI1 CS / UART0 RX / I2C0 SCL / PWM6 B / ADC3
Make sure C120 is close to pin 44 of RP2040
Make sure C130 is close to pin 45 of RP2040
GP18: SPI0 SCK / UART0 CTS / I2C1 SDA / PWM1 A
GP27: SPI1 TX / UART1 RTS / I2C1 SCL / PWM5 B / ADC1
GP17: SPI0 CS / UART0 RX / I2C0 SCL / PWM0 B
GP26: SPI1 SCK / UART1 CTS / I2C1 SDA / PWM5 A / ADC0
Flash

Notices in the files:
hardware/EDA-Files/REG1-App-Eth/REG1-App-Eth.kicad_sch:
OpenKNX Open Hardware under CC BY-NC-SA 4.0
hardware/EDA-Files/REG1-Front-Universal/REG1-Front-Universal_catia.kicad_pcb:
V00.02 © Ing-Dom, 2022
hardware/EDA-Files/REG1-IpController2040/REG1-IpController2040.kicad_pcb:
© Ing-Dom, 2023
